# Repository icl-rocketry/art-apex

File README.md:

# art-apex
PCBs and software for ART's APEX rocket

# Contents

1. [Hardware](#Hardware)
2. [Software architecture](#SoftwareArchitecture)
3. [Next Steps](#NextSteps)

## Hardware

The flight computer for Apex consists of the following components:

1. [Tiny2040](https://shop.pimoroni.com/products/tiny-2040) microcontroller - for controlling each of the components
2. [BNO085](https://learn.adafruit.com/adafruit-9-dof-orientation-imu-fusion-breakout-bno085) 9DoF IMU - for recording and fusing flight data
3. [DPS310](https://www.infineon.com/cms/en/product/sensor/pressure-sensors/pressure-sensors-for-iot/dps310/) barometer - for recording altitude information
4. [Sim800L](https://nettigo.eu/products/sim800l-gsm-grps-module) GPRS/GSM module - for communication between the flight computer and ground team
5. [Adafruit mini GPS PA1010D](https://www.adafruit.com/product/4415) GPS module - for recovery
6. 3.7V 200maH LiPo battery - for powering the system
7. A 104 decibel speaker - for recovery

The Tiny2040 is connected to the BNO085, DPS310 and PA1010D via an I2C connection using GPIO pins 26 and 27. The Tiny2040 is connected to the Sim800L module via a UART connection using GPIO pins 4 and 5.

The SIM8000L **must** be isolated when the Tiny2040 is connected to USB, or else it will be fried.

## Software

The filesystem on board the Tiny2040 will look like this:
```
📦src
 ┣ 📂lib
 ┃ ┣ 📂adafruit_bno08x
 ┃ ┃ ┣ 📜debug.py
 ┃ ┃ ┣ 📜i2c.py
 ┃ ┃ ┗ 📜__init__.py
 ┃ ┣ 📂adafruit_bus_device
 ┃ ┃ ┣ 📜i2c_device.mpy
 ┃ ┃ ┣ 📜spi_device.mpy
 ┃ ┃ ┗ 📜__init__.py
 ┃ ┣ 📂adafruit_register
 ┃ ┃ ┣ 📜i2c_bcd_alarm.mpy
 ┃ ┃ ┣ 📜i2c_bcd_datetime.mpy
 ┃ ┃ ┣ 📜i2c_bit.mpy
 ┃ ┃ ┣ 📜i2c_bits.mpy
 ┃ ┃ ┣ 📜i2c_struct.mpy
 ┃ ┃ ┣ 📜i2c_struct_array.mpy
 ┃ ┃ ┗ 📜__init__.py
 ┃ ┣ 📜adafruit_dps310.mpy
 ┃ ┗ 📜adafruit_gps.py
 ┣ 📜boot.py
 ┣ 📜code.py
 ┣ 📜gps.py
 ┣ 📜led.py
 ┣ 📜phone.number
 ┣ 📜sensors.py
 ┣ 📜sms.py
 ┣ 📜speaker.py
 ┗ 📜state_machine.py
```

All folders inside the lib directory are libraries required for the Tiny2040 to interact with components. None of these files should be changed, except for lib/adafruit_bno08x/\_\_init__.py, where `_DEFAULT_REPORT_INTERVAL` should be set to 35ms. **Pro tip: don't lower this if you want to launch**.

`boot.py` runs right after the Tiny2040 boots up. Its sole purpose is to grant write permission to the Tiny2040. Due to the implementation of CircuitPython's filesystem either a laptop or the Tiny2040, can write to the Tiny2040's filesystem, so this ensures that the Tiny2040 has this permission.

`code.py` runs the main code of the AAS. It essentially runs through the state machine defined in `state_machine.py`.

`gps.py`, `led.py`, `sensors.py`, `speaker.py` and `sms.py` are [adapters](https://www.tutorialspoint.com/design_pattern/adapter_pattern.htm) around the peripherals discussed above. The adapter pattern is used to decouple the rest of the code from the specifics of these devices.

`state_machine.py` contains the bulk of the flight logic. It describes a (linear) [finite state machine](https://en.wikipedia.org/wiki/Finite-state_machine) with 5 states.

1. Diagnostic - initialises sensors and sends initial messages
2. Calibration - calibrates the BNO085 as described [here](https://www.ceva-dsp.com/wp-content/uploads/2019/10/BNO080_085-Datasheet.pdf) on page 39
3. Preflight - sleeps until the launch command is sent.
4. Flight - records 5 minutes of flight data, and sends data to the telemetry service.
5. Postflight - sends the rocket's location/plays the siren when asked. Also plays the siren once every 30 seconds.

The Flight stage is the most involved, so a brief explanation of its code can be found below.

```py
def run(self):
    i = 0
    led.colour(255, 0, 0)

    #Problem:
    #Sim module will need long (50ms+) waits to work
    #But we can't afford that in a single threaded environment
    #Solution:
    #Use pkt_wait to provide the sleeps
    pkt_wait = 1
    pkt = bytearray(sensors.data_size * 4)
    self._sms.connect()

    while i < self._flight_time:
        pkt_wait -= 1
        i += 1
        start = millis()
        data = self._sensors.get()
        for reading in data:
            self._sensor_storage.write(struct.pack("f", reading))

        if pkt_wait == 0:
            pkt[0:4] = struct.pack("f", data[0]) #time
            for j in range(4):
                pkt[4*j:4*(j+1)] = struct.pack("f", data[j+4])
            
            pkt[20:24] = struct.pack("f", data[10]) #altitude
            pkt_wait = self._sms.send_pkt(pkt)
        end = millis()
        sleep_ms(max(0, self._delay - (end - start)))

    self._sensor_storage.flush()
    self._sensor_storage.close()
    self._sms.disconnect()
    return postflight(self._sms, self._gps)
```

```py
led.colour(255, 0, 0)
```
First the Tiny2040's led is set to red to indicate flight.

```py
pkt_wait = 1
pkt = bytearray(sensors.data_size * 4)
self._sms.connect()
```
This code relates to the telemetry service. The Sim800L will connect to GPRS here (the internet) and send appropriate data via UDP. To save space, it will group several readings into a single packet.

```py
while i < self._flight_time:
    pkt_wait -= 1
    i += 1
    start = millis()
    data = self._sensors.get()
    for reading in data:
        self._sensor_storage.write(struct.pack("f", reading))

    if pkt_wait == 0:
        pkt[0:4] = struct.pack("f", data[0]) #time
        for j in range(4):
            pkt[4*j:4*(j+1)] = struct.pack("f", data[j+4])
        
        pkt[20:24] = struct.pack("f", data[10]) #altitude
        pkt_wait = self._sms.send_pkt(pkt)
    end = millis()
    sleep_ms(max(0, self._delay - (end - start)))
```

This is the main flight loop. It waits for `self._flight_time` readings to occur (assuming each reading takes at most `self._delay` ms).

```py
start = millis()
data = self._sensors.get()
for reading in data:
    self._sensor_storage.write(struct.pack("f", reading))
```
This code takes sensor readings, and records the time that they were taken, then writes them into a file. The values are stored as 32bit floating point numbers, to save space.
Note: the time recorded is milliseconds from the start.

```py
if pkt_wait == 0:
    pkt[0:4] = struct.pack("f", data[0]) #time
    for j in range(4):
        pkt[4*j:4*(j+1)] = struct.pack("f", data[j+4])
    
    pkt[20:24] = struct.pack("f", data[10]) #altitude
    pkt_wait = self._sms.send_pkt(pkt)
```
This adds the readings into the packet defined earlier, and if the packet is full it sends them.

The `pkt_wait` variable is used to solve a problem, which is that the Sim800l needs to wait around 200ms after it's sent a packet, before being able to send another one. However we can't perform this wait in the main loop, as that would lead to large delays in between recordings, so we define the `pkt_wait` variable to indicate whether we can send a packet. This allows us to use the main loop as a pseudo sleep (at the time of writing, the `uasynchio` library was not available).

```py
end = millis()
sleep_ms(max(0, self._delay - (end - start)))
```
This ensures that we always sleep for at least 50ms, regardless of how long different components take to work.

```py
self._sensor_storage.flush()
self._sensor_storage.close()
self._sms.disconnect()
return postflight(self._sms, self._gps)
```
Finally we flush the recordings, and close the file, then disconnect the Sim800L from GPRS and move on to the postflight stage.

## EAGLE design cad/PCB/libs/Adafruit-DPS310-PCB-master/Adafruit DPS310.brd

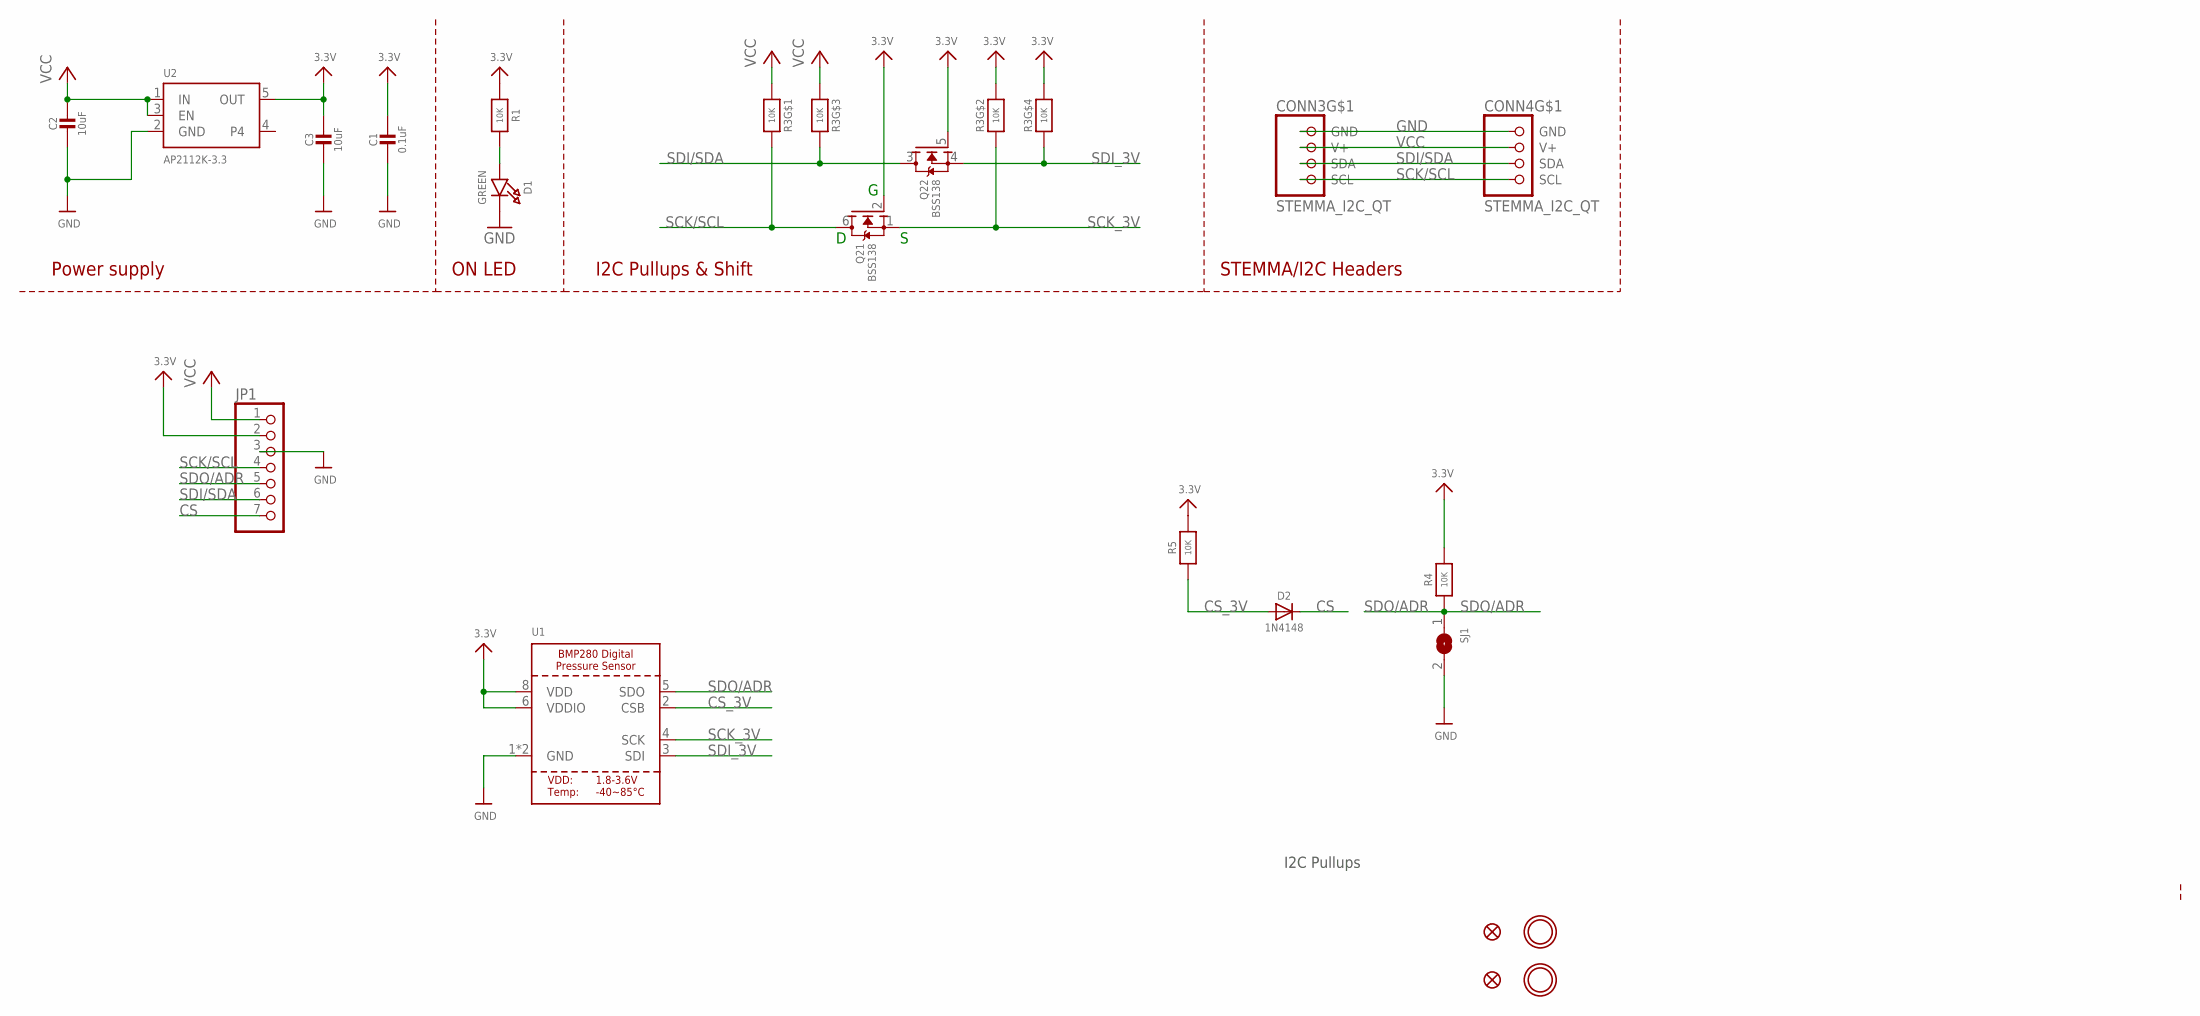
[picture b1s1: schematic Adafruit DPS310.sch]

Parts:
C1: 0.1uF; 0603-NO
C2, C3: 10uF; 0805-NO
CONN3, CONN4: STEMMA_I2C_QT; JST_SH4
D1: GREEN; CHIPLED_0603_NOOUTLINE
D2: 1N4148; SOD-323
FID3, FID4: FIDUCIAL_1MM
JP1: HEADER-1X770MIL; 1X07_ROUND_70
Q2: BSS138; SOT363
R1, R4, R5: 10K; 0603-NO
R3: 10K; RESPACK_4X0603
SJ1: SOLDERJUMPER; SOLDERJUMPER_ARROW_NOPASTE
U1: BMP280_COMBO; BMX280_COMBO
U2: AP2112K-3.3; SOT23-5
U$1, U$17: MOUNTINGHOLE2.5; MOUNTINGHOLE_2.5_PLATED

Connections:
3.3V: C1.1, C3.1, JP1.2, Q2.2 (G), Q2.5 (G), R1.1, R3.2 (1), R3.4 (1), R4.2, R5.2, U1.6 (VDDIO), U1.8 (VDD), U2.5 (OUT)
CS: D2.C, JP1.7
CS_3V: D2.A, R5.1, U1.2 (CSB)
GND: C1.2, C2.2, C3.2, CONN3.1 (GND), CONN4.1 (GND), D1.C, JP1.3, SJ1.2, U1.1 (GND), U1.7 (GND), U2.2 (GND)
unnamed: D1.A, R1.2
SCK/SCL: CONN3.4 (SCL), CONN4.4 (SCL), JP1.4, Q2.6 (D), R3.8 (2)
SCK_3V: Q2.1 (S), R3.7 (2), U1.4 (SCK)
SDI/SDA: CONN3.3 (SDA), CONN4.3 (SDA), JP1.6, Q2.3 (D), R3.6 (2)
SDI_3V: Q2.4 (S), R3.5 (2), U1.3 (SDI)
SDO/ADR: JP1.5, R4.1, SJ1.1, U1.5 (SDO)
VCC: C2.1, CONN3.2 (V+), CONN4.2 (V+), JP1.1, R3.1, R3.3 (1), U2.1 (IN), U2.3 (EN)

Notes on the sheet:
I2C Pullups & Shift
STEMMA/I2C Headers
ON LED
Power supply
I2C Pullups

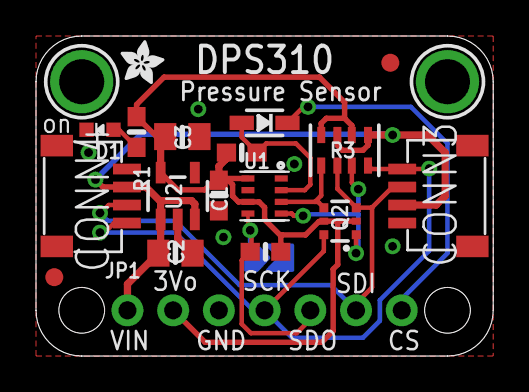
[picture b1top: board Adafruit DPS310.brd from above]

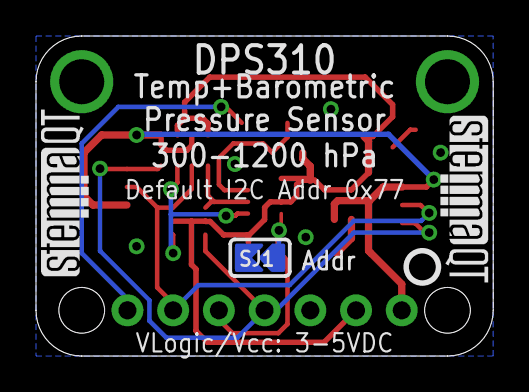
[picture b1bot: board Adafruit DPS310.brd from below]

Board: 2 copper layers, 25.4 x 17.8 mm, 24 parts (4 on the bottom side), 11 nets.

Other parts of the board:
U$4: ADAFRUIT_2.5MM
U$25: PCBFEAT-REV-040
U$30, U$31: STEMMAQT

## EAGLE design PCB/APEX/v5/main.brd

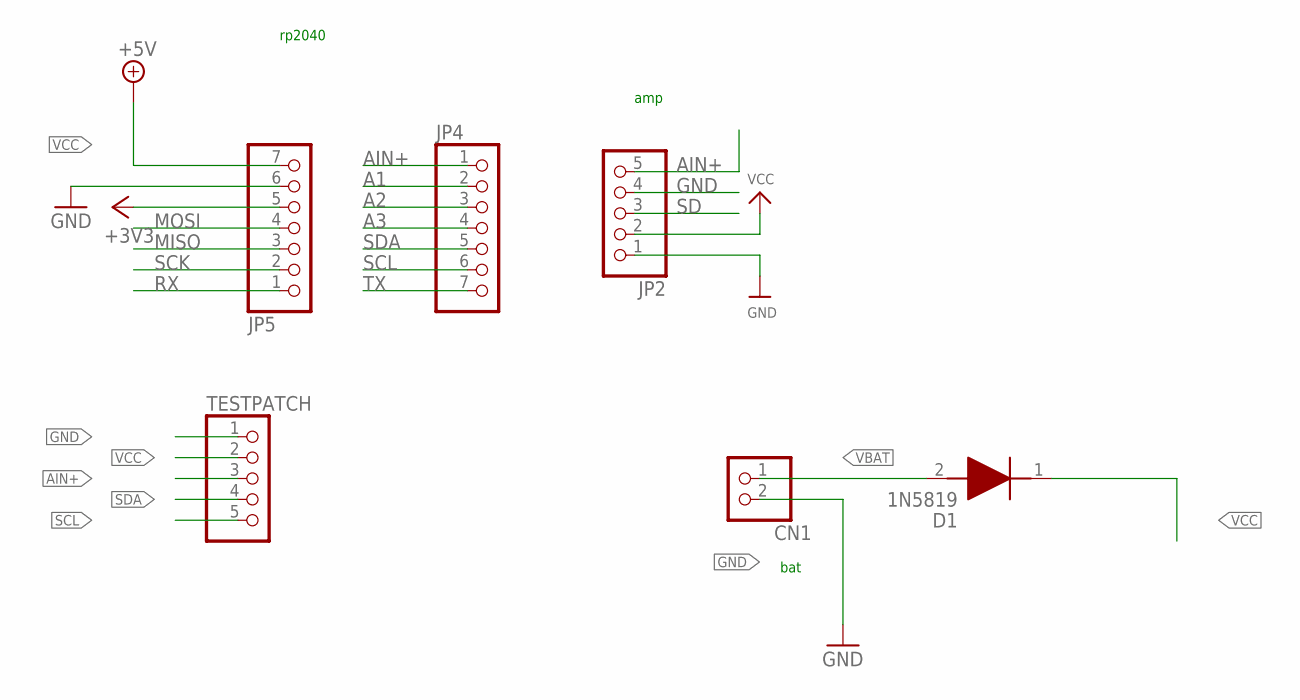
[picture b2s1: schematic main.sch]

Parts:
CN1: JST_2PIN-THM; JST-PH-2-THM
D1: 1N5819; DIOAD1414W86L464D238
JP2: HEADER-1X570MIL; 1X05_ROUND_70
JP4, JP5: HEADER-1X7; 1X07_OVAL
TESTPATCH: PINHD-1X5; 1X05

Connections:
+3V3: JP5.5
A1: JP4.2
A2: JP4.3
A3: JP4.4
AIN+: JP2.5, JP4.1, TESTPATCH.3
GND: CN1.2 (1), JP2.1, JP2.4, JP5.6, TESTPATCH.1
MISO: JP5.3
MOSI: JP5.4
RX: JP5.1
SCK: JP5.2
SCL: JP4.6, TESTPATCH.5
SD: JP2.3
SDA: JP4.5, TESTPATCH.4
TX: JP4.7
VBAT: CN1.1 (2), D1.2 (A)
VCC: D1.1 (K), JP2.2, JP5.7, TESTPATCH.2

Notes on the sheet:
amp
bat
rp2040

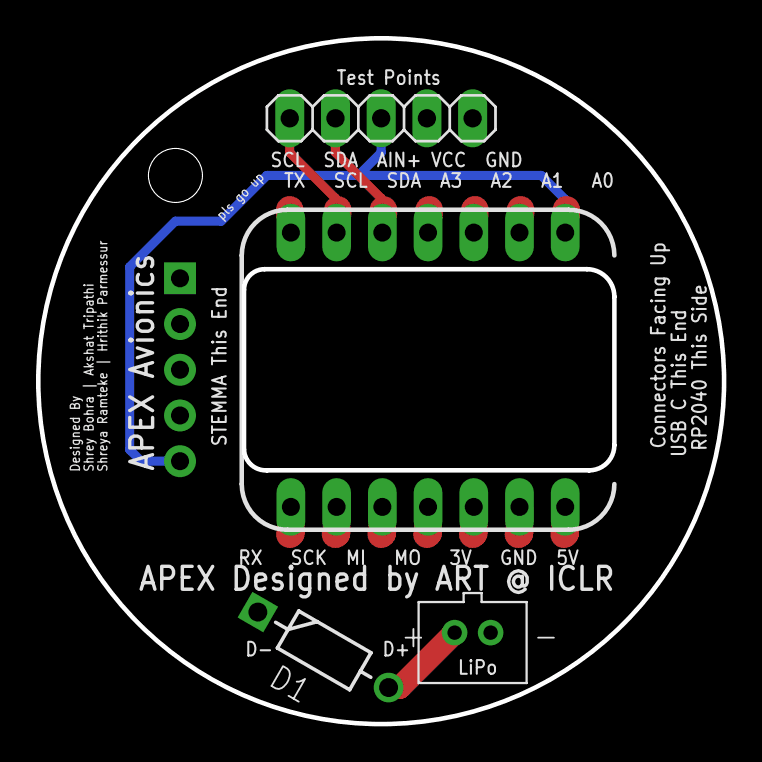
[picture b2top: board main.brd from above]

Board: 2 copper layers, 38.1 x 38.1 mm, 6 parts (1 on the bottom side), 6 nets.

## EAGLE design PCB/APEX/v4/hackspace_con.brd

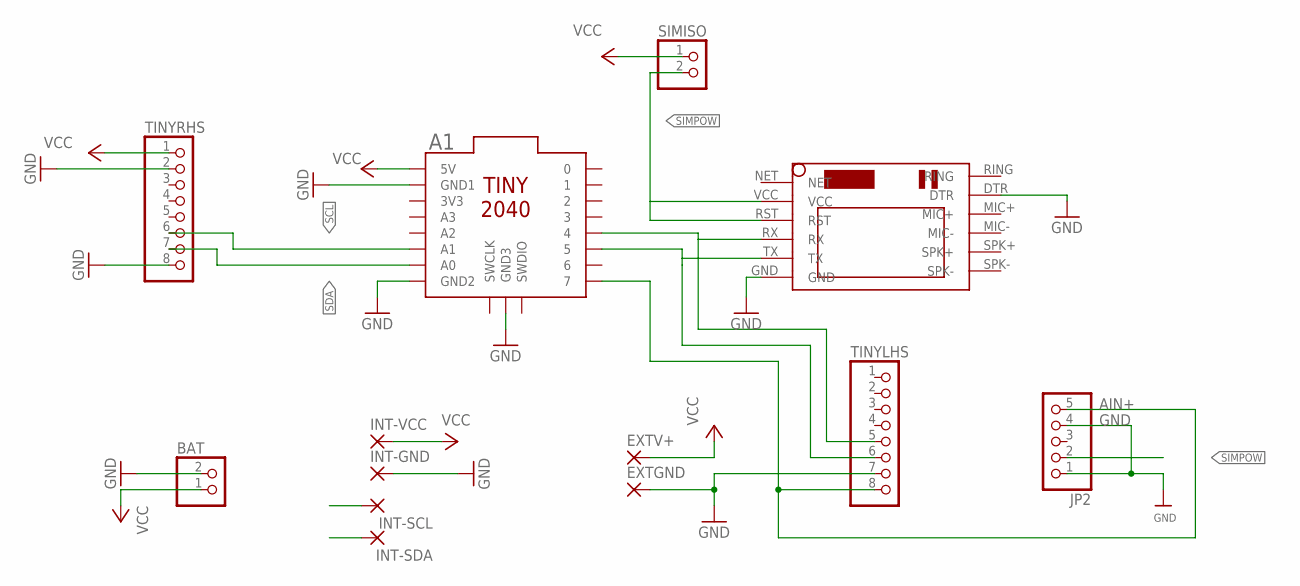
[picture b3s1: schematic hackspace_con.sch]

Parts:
A1: TINY2040
BAT: JST_2PIN-THM-RA; JST-PH-2-THM-RA
EXTGND: SMD5; SMD2,54-5,08
EXTV+: SMD5; SMD2,54-5,08
INT-GND: 3,17/1,1
INT-SCL: 3,17/1,1
INT-SDA: 3,17/1,1
INT-VCC: 3,17/1,1
JP2: HEADER-1X570MIL; 1X05_ROUND_70
SIMISO: PINHD-1X2; 1X02
TINYLHS: PINHD-1X8; 1X08
TINYRHS: PINHD-1X8; 1X08
U$1: SIM800LMODULE

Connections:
AIN+: A1.7, JP2.5, TINYLHS.8
GND: A1.GND1, A1.GND2, A1.GND3, BAT.2 (1), EXTGND.1, INT-GND.1, JP2.1, JP2.4, TINYLHS.7, TINYRHS.2, TINYRHS.8, U$1.DTR, U$1.GND
RX: A1.4, TINYLHS.5, U$1.RX
SCL: A1.A1, INT-SCL.1, TINYRHS.6
SDA: A1.A0, INT-SDA.1, TINYRHS.7
SIMPOW: JP2.2, SIMISO.2, U$1.RST, U$1.VCC
TX: A1.5, TINYLHS.6, U$1.TX
VCC: A1.5V, BAT.1 (2), EXTV+.1, INT-VCC.1, SIMISO.1, TINYRHS.1

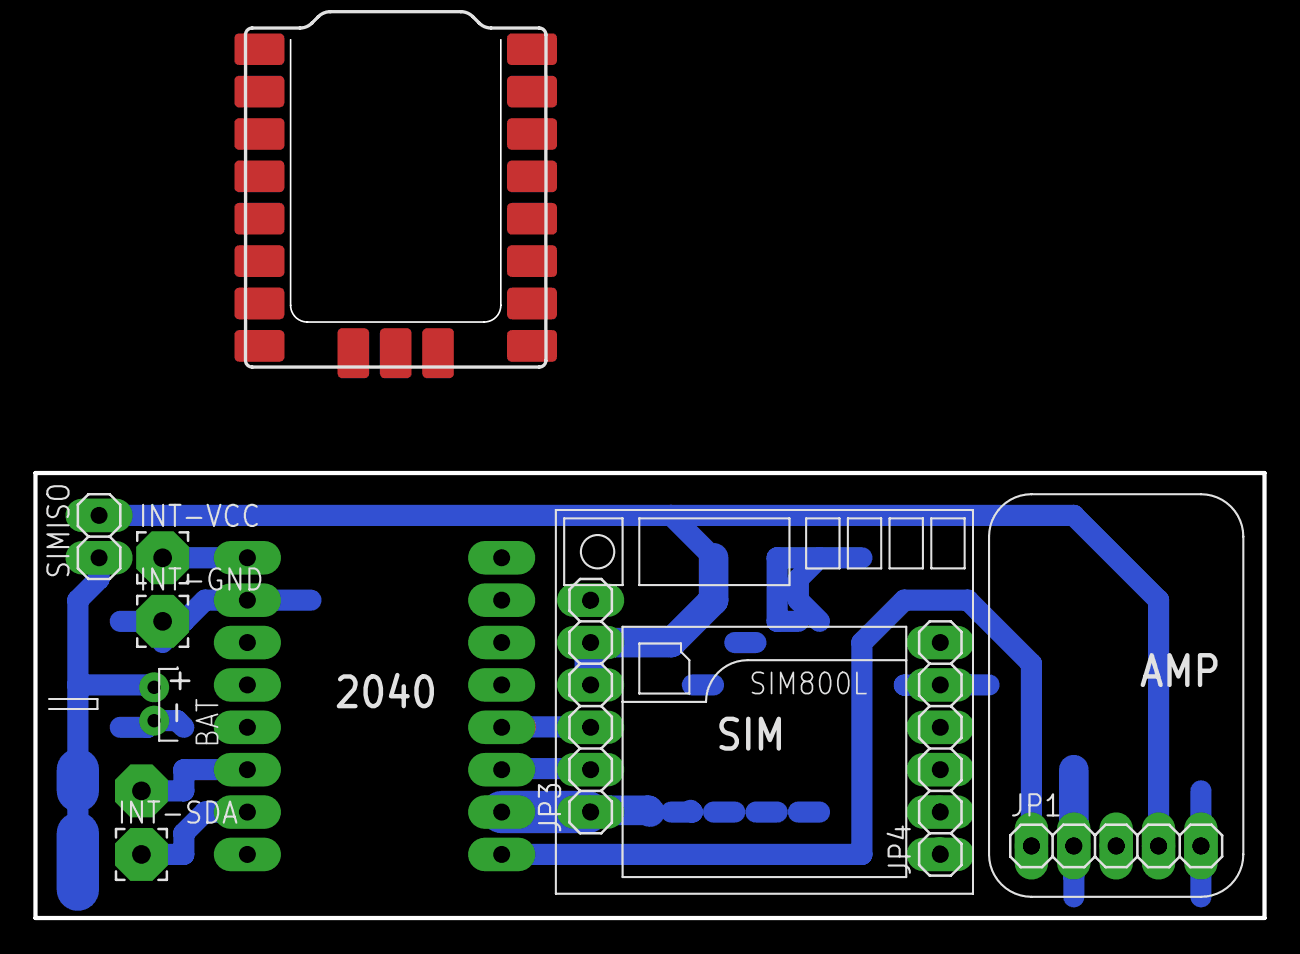
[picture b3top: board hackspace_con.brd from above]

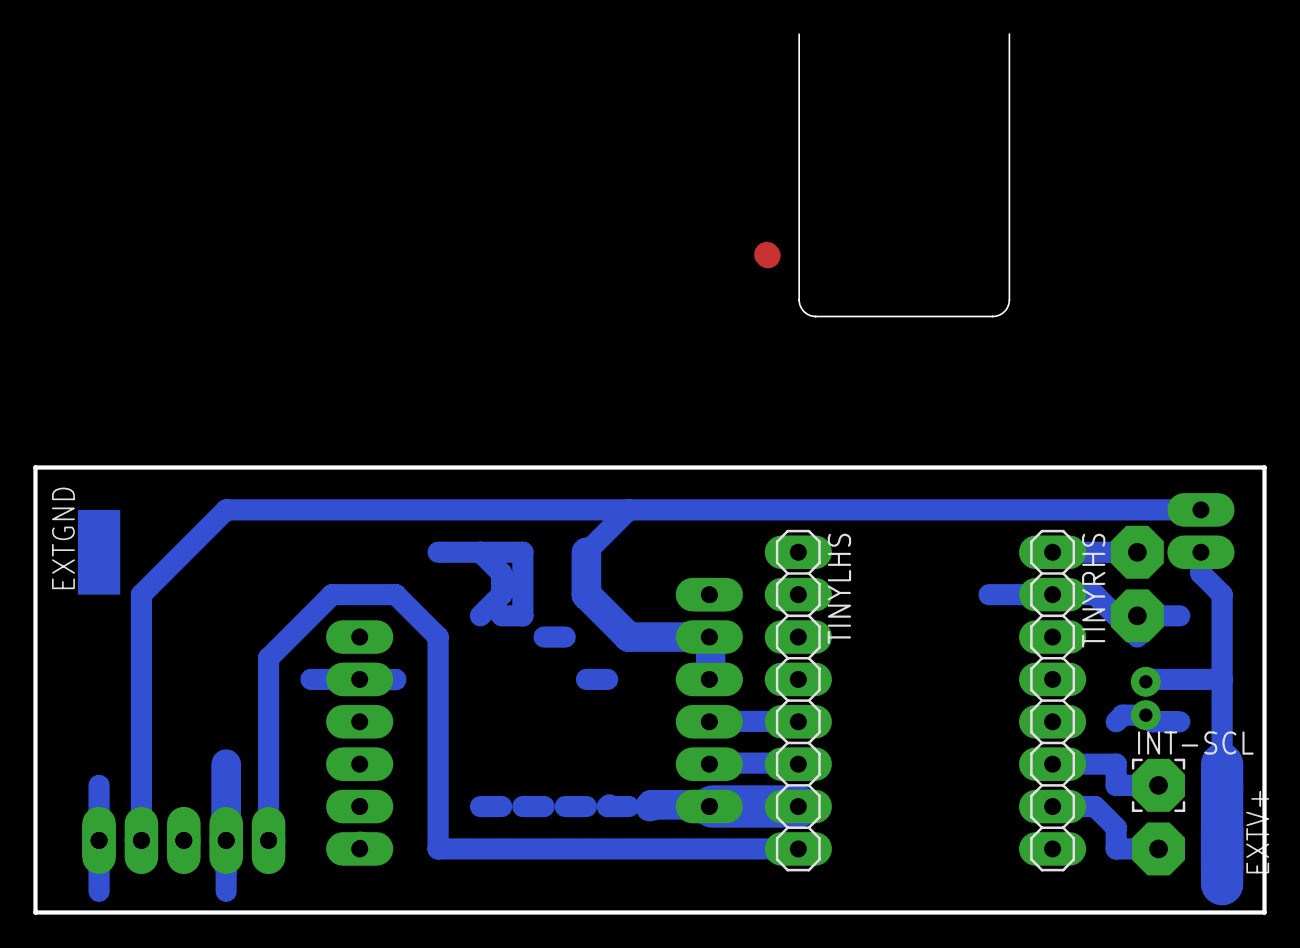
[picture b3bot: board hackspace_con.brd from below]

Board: 2 copper layers, 73.7 x 26.7 mm, 16 parts (5 on the bottom side), 8 nets.

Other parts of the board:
JP1: 1X05
JP3, JP4: 1X06

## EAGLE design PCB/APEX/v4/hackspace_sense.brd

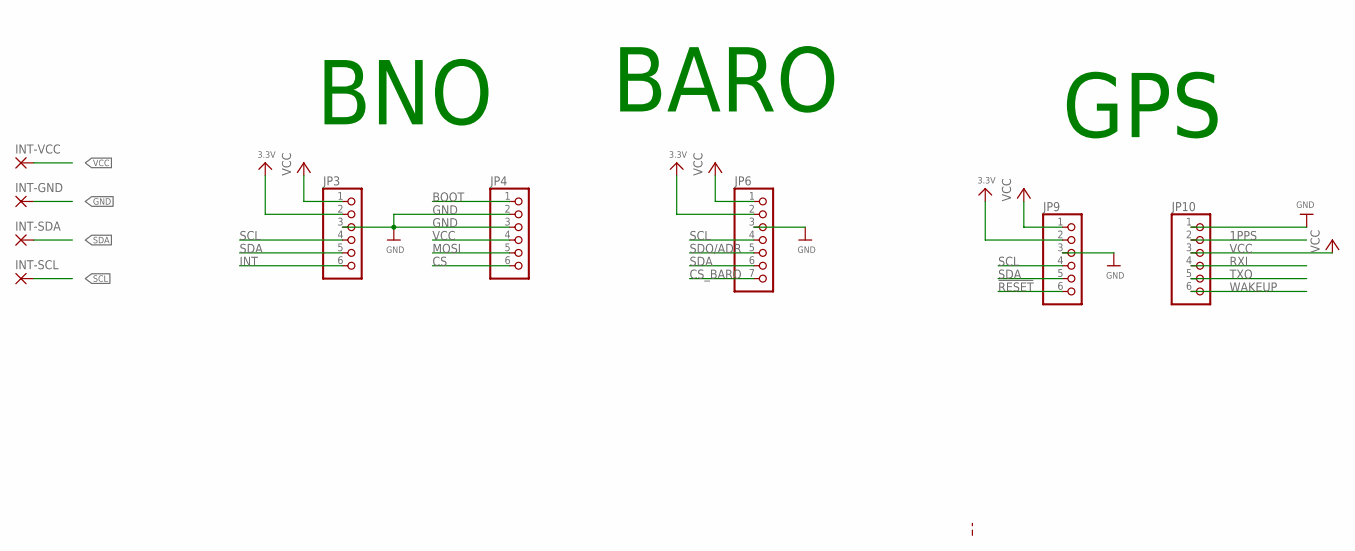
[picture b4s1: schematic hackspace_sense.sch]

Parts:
INT-GND: 3,17/1,1
INT-SCL: 3,17/1,1
INT-SDA: 3,17/1,1
INT-VCC: 3,17/1,1
JP3, JP4, JP9, JP10: HEADER-1X670MIL; 1X06_ROUND_70
JP6: HEADER-1X770MIL; 1X07_ROUND_70

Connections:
1PPS: JP10.2
3.3V_BARO: JP6.2
3.3V_BNO: JP3.2
3.3V_GPS: JP9.2
!RESET: JP9.6
BOOT: JP4.1
CS: JP4.6
CS_BARO: JP6.7
GND: INT-GND.1, JP3.3, JP4.2, JP4.3, JP6.3, JP9.3, JP10.1
INT: JP3.6
MOSI: JP4.5
RXI: JP10.4
SCL: INT-SCL.1, JP3.4, JP6.4, JP9.4
SDA: INT-SDA.1, JP3.5, JP6.6, JP9.5
SDO/ADR: JP6.5
TXO: JP10.5
VCC: INT-VCC.1, JP3.1, JP4.4, JP6.1, JP9.1, JP10.3
WAKEUP: JP10.6

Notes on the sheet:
BNO
BARO
GPS

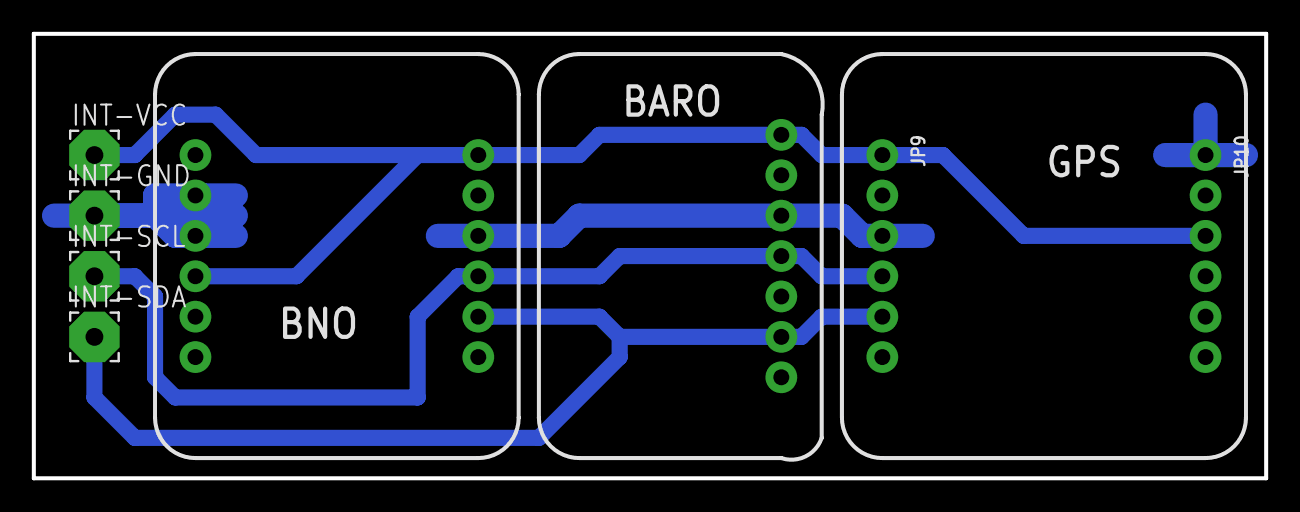
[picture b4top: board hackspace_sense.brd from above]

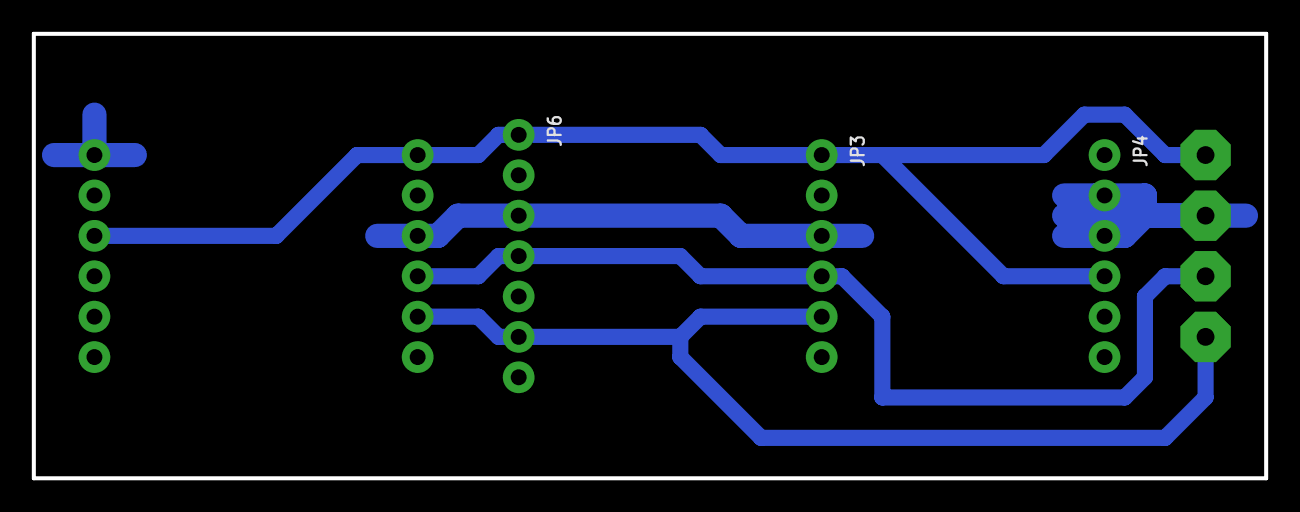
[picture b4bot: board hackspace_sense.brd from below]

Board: 2 copper layers, 77.5 x 27.9 mm, 9 parts (3 on the bottom side), 4 nets.

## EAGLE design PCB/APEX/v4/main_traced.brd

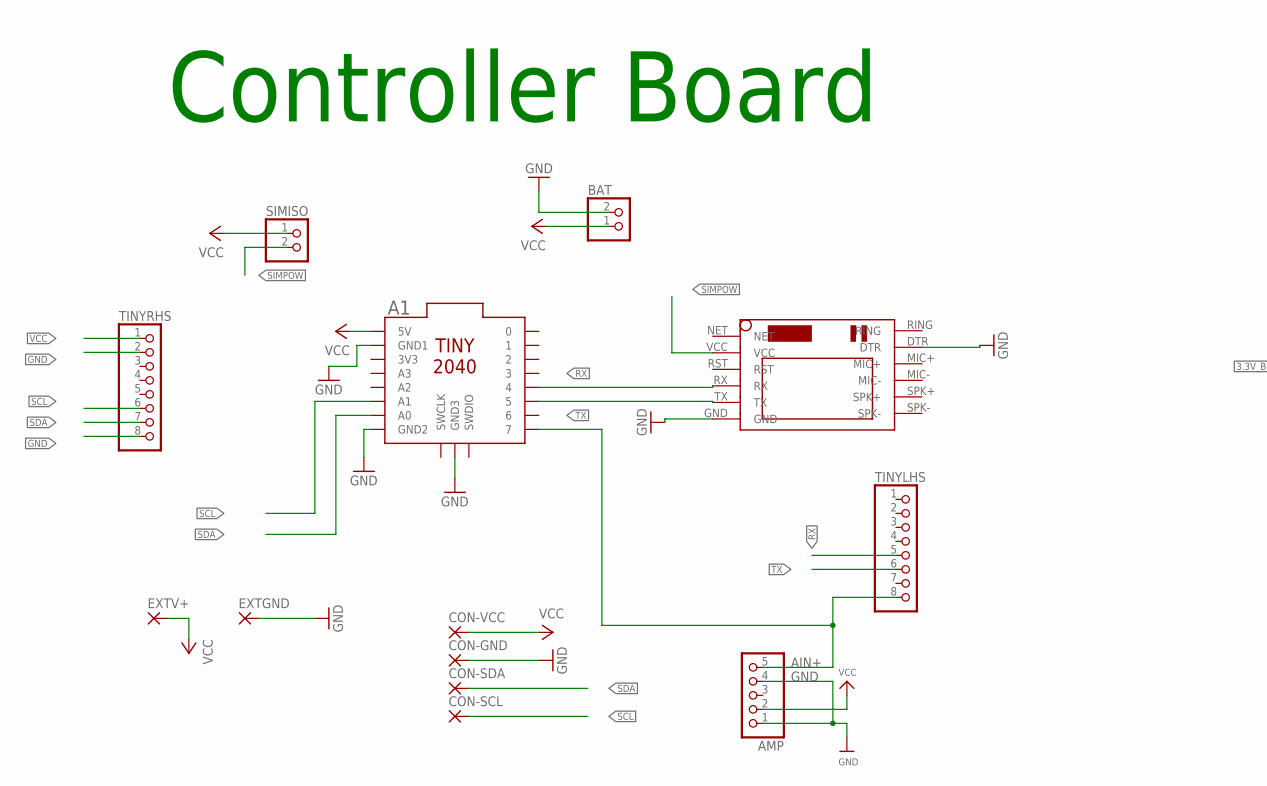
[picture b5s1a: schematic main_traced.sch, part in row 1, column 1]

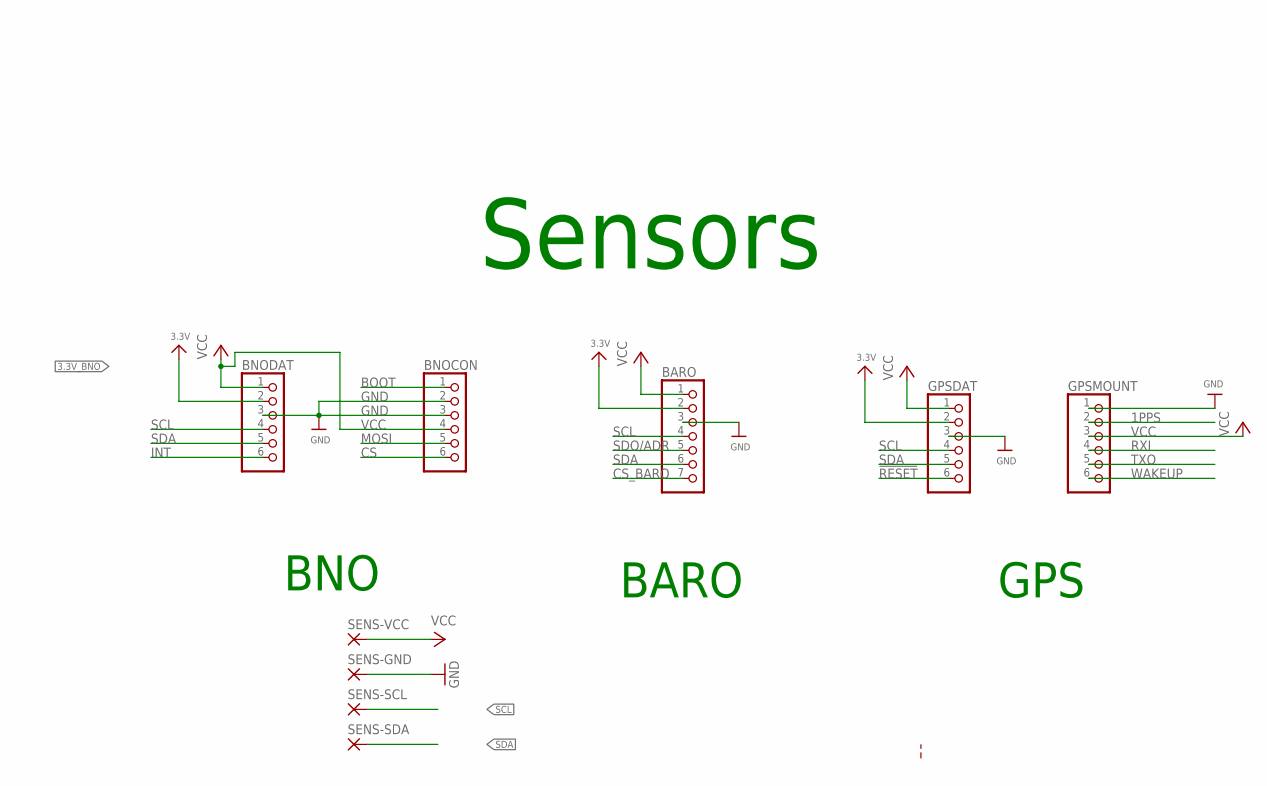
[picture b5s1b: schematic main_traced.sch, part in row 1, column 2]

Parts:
A1: TINY2040
AMP: HEADER-1X570MIL; 1X05_ROUND_70
BARO: HEADER-1X770MIL; 1X07_ROUND_70
BAT: JST_2PIN-THM-RA; JST-PH-2-THM-RA
BNOCON: HEADER-1X670MIL; 1X06_ROUND_70
BNODAT: HEADER-1X670MIL; 1X06_ROUND_70
CON-GND: 3,17/1,3
CON-SCL: 3,17/1,3
CON-SDA: 3,17/1,3
CON-VCC: 3,17/1,3
EXTGND: SMD5; SMD2,54-5,08
EXTV+: SMD5; SMD2,54-5,08
GPSDAT: HEADER-1X670MIL; 1X06_ROUND_70
GPSMOUNT: HEADER-1X670MIL; 1X06_ROUND_70
SENS-GND: 3,17/1,3
SENS-SCL: 3,17/1,3
SENS-SDA: 3,17/1,3
SENS-VCC: 3,17/1,3
SIMISO: PINHD-1X2; 1X02
TINYLHS: PINHD-1X8; 1X08
TINYRHS: PINHD-1X8; 1X08
U$1: SIM800LMODULE

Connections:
1PPS: GPSMOUNT.2
3.3V_2: BARO.2
3.3V_3: GPSDAT.2
3.3V_BNO: BNODAT.2
!RESET: GPSDAT.6
AIN+: A1.7, AMP.5, TINYLHS.8
BOOT: BNOCON.1
CS: BNOCON.6
CS_BARO: BARO.7
GND: A1.GND1, A1.GND2, A1.GND3, AMP.1, AMP.4, BARO.3, BAT.2 (1), BNOCON.2, BNOCON.3, BNODAT.3, CON-GND.1, EXTGND.1, GPSDAT.3, GPSMOUNT.1, SENS-GND.1, TINYRHS.2, TINYRHS.8, U$1.DTR, U$1.GND
INT: BNODAT.6
MOSI: BNOCON.5
RX: A1.4, TINYLHS.5, U$1.RX
RXI: GPSMOUNT.4
SCL: A1.A1, BARO.4, BNODAT.4, CON-SCL.1, GPSDAT.4, SENS-SCL.1, TINYRHS.6
SDA: A1.A0, BARO.6, BNODAT.5, CON-SDA.1, GPSDAT.5, SENS-SDA.1, TINYRHS.7
SDO/ADR: BARO.5
SIMPOW: SIMISO.2, U$1.RST, U$1.VCC
TX: A1.5, TINYLHS.6, U$1.TX
TXO: GPSMOUNT.5
VCC: A1.5V, AMP.2, BARO.1, BAT.1 (2), BNOCON.4, BNODAT.1, CON-VCC.1, EXTV+.1, GPSDAT.1, GPSMOUNT.3, SENS-VCC.1, SIMISO.1, TINYRHS.1
WAKEUP: GPSMOUNT.6

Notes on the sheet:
Controller Board
BNO
BARO
GPS
Sensors

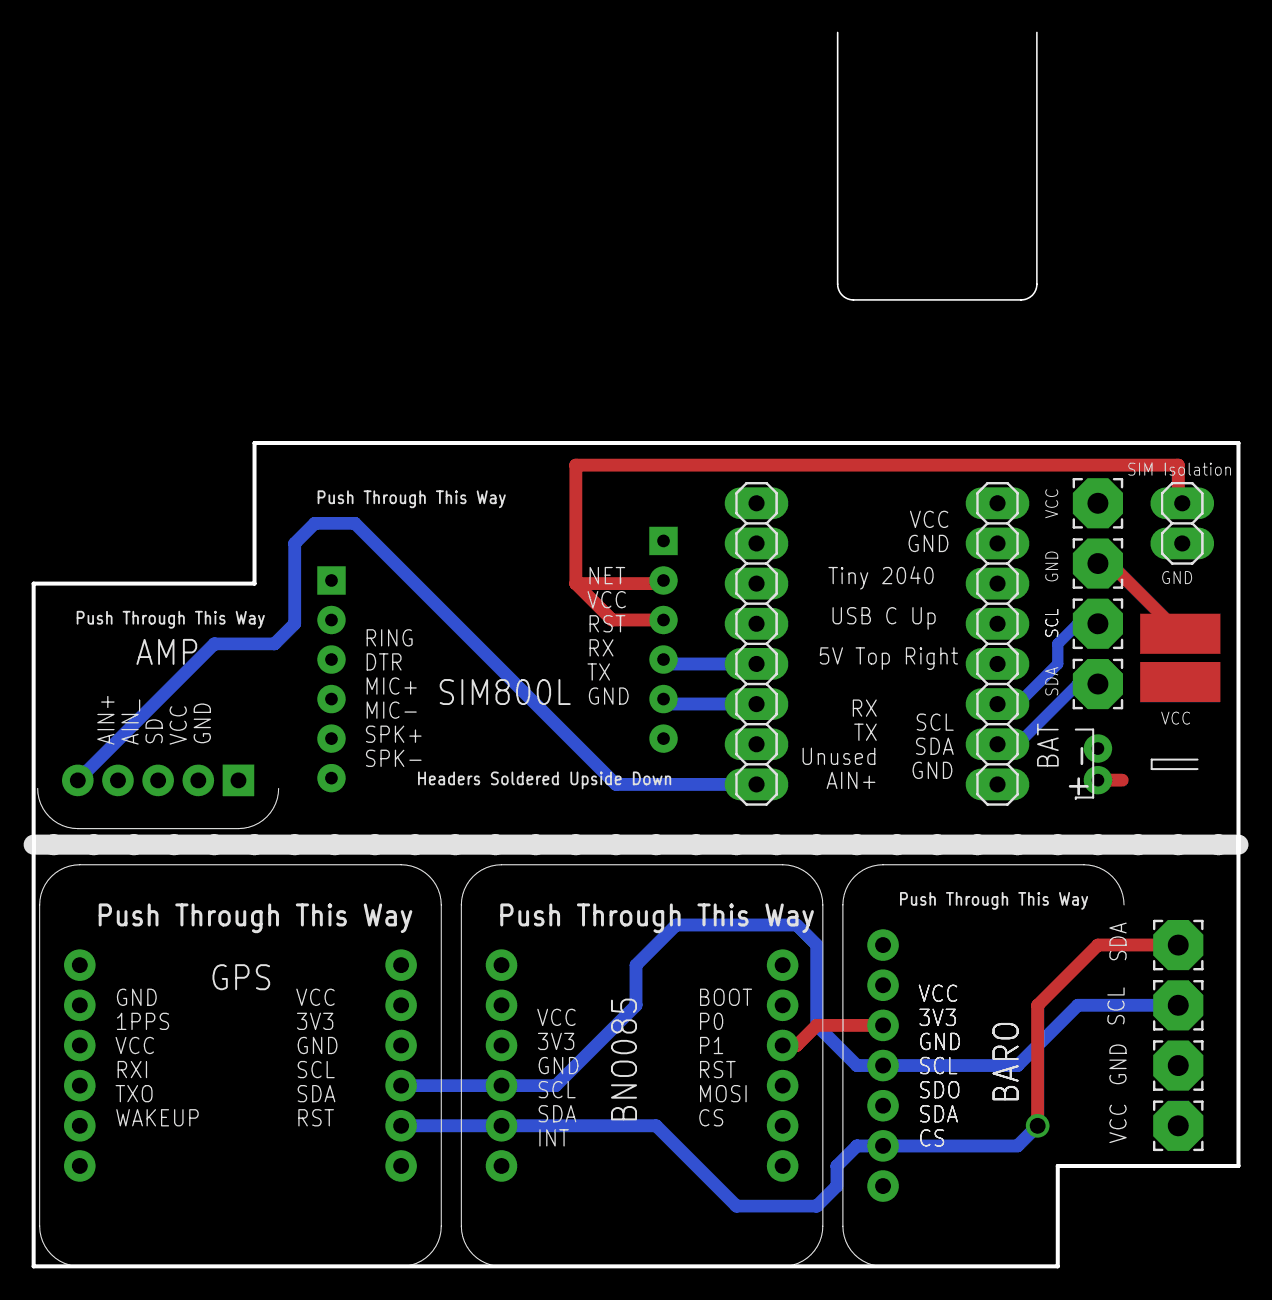
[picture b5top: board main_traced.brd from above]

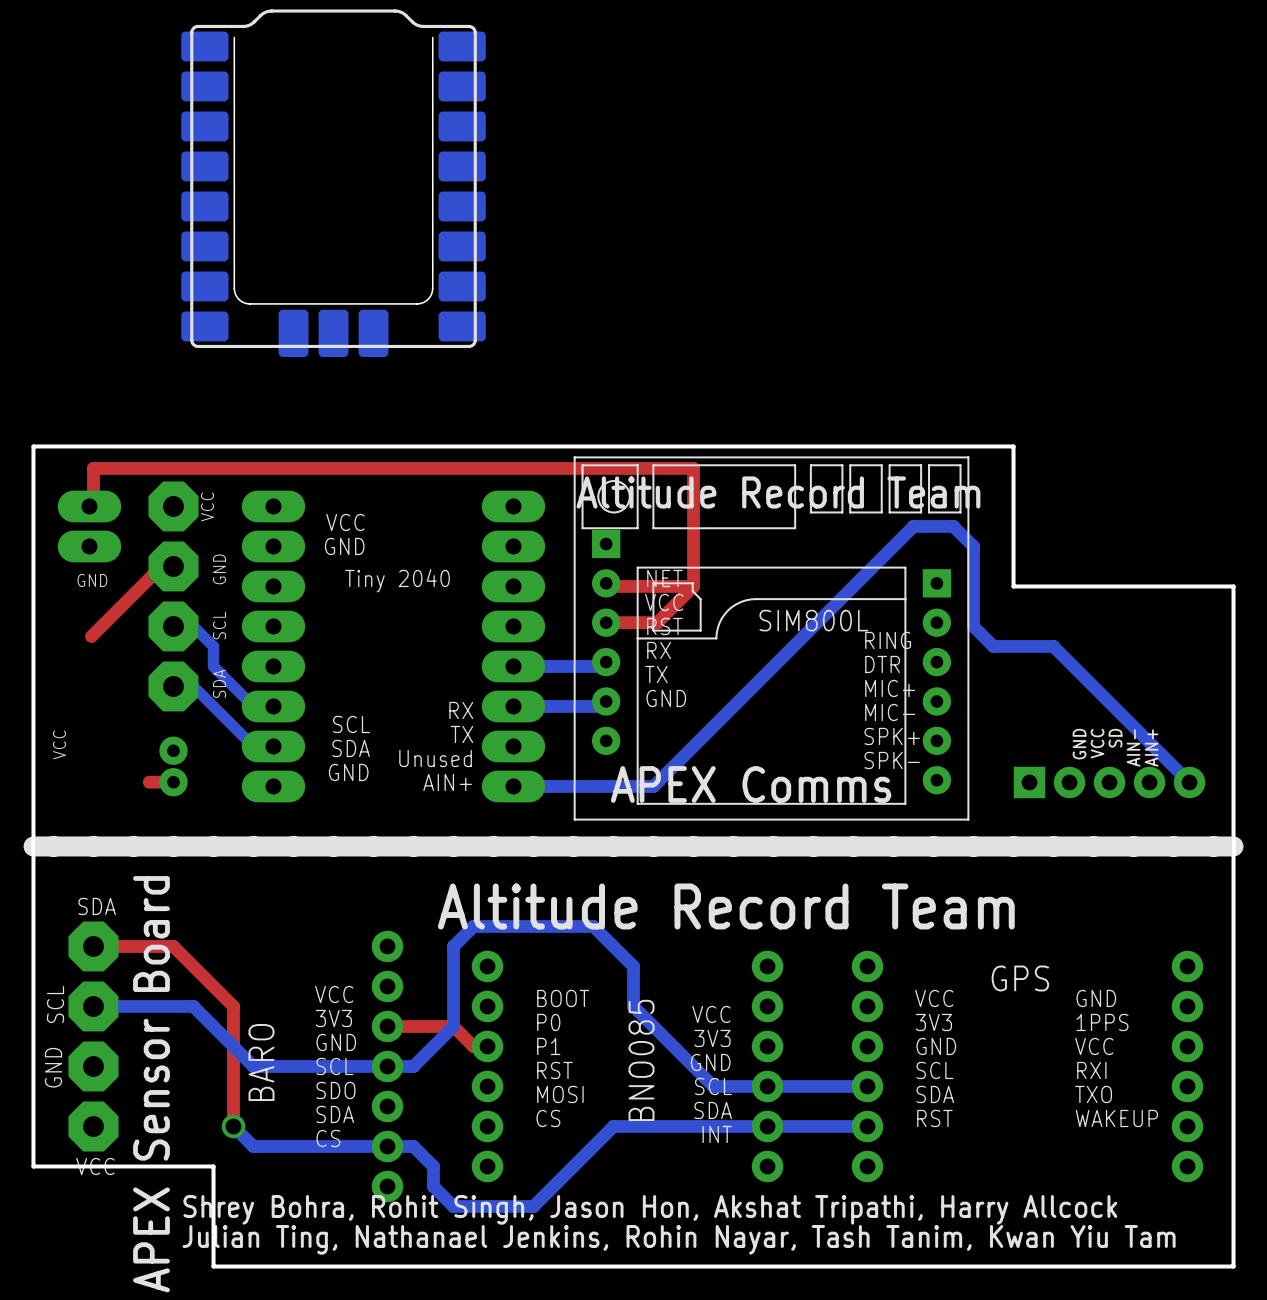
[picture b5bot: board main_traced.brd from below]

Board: 2 copper layers, 76.2 x 52.1 mm, 22 parts (4 on the bottom side), 8 nets.

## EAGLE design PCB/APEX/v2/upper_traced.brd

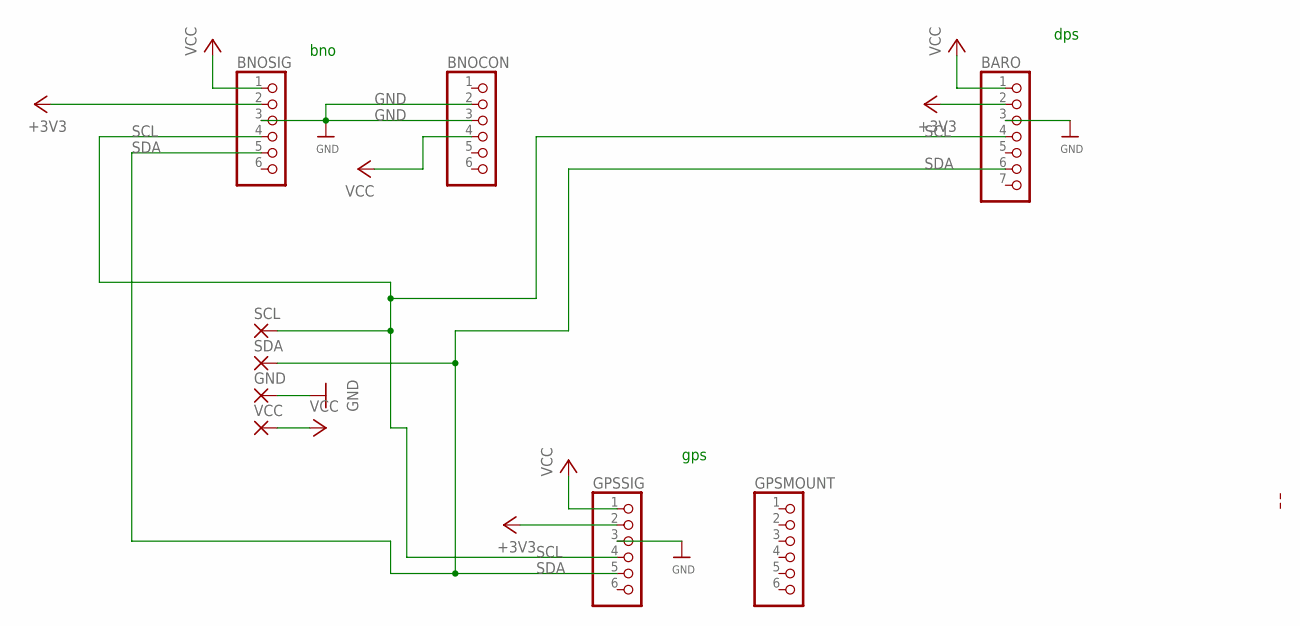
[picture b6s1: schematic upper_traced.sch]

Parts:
BARO: HEADER-1X770MIL; 1X07_ROUND_70
BNOCON: HEADER-1X670MIL; 1X06_ROUND_70
BNOSIG: HEADER-1X670MIL; 1X06_ROUND_70
GND: 3,17/1,1
GPSMOUNT: HEADER-1X670MIL; 1X06_ROUND_70
GPSSIG: HEADER-1X670MIL; 1X06_ROUND_70
SCL: 3,17/1,1
SDA: 3,17/1,1
VCC: 3,17/1,1

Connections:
+3V3: BARO.2, BNOSIG.2, GPSSIG.2
GND: BARO.3, BNOCON.2, BNOCON.3, BNOSIG.3, GND.1, GPSMOUNT.1, GPSSIG.3
SCL: BARO.4, BNOSIG.4, GPSSIG.4, SCL.1
SDA: BARO.6, BNOSIG.5, GPSSIG.5, SDA.1
VCC: BARO.1, BNOCON.4, BNOSIG.1, GPSMOUNT.3, GPSSIG.1, VCC.1

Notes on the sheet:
bno
dps
gps

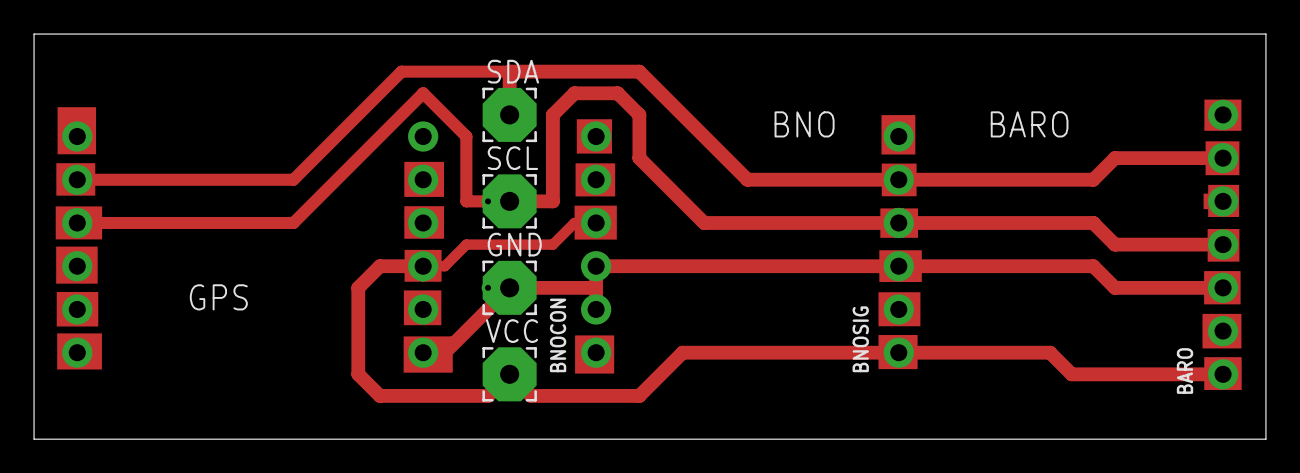
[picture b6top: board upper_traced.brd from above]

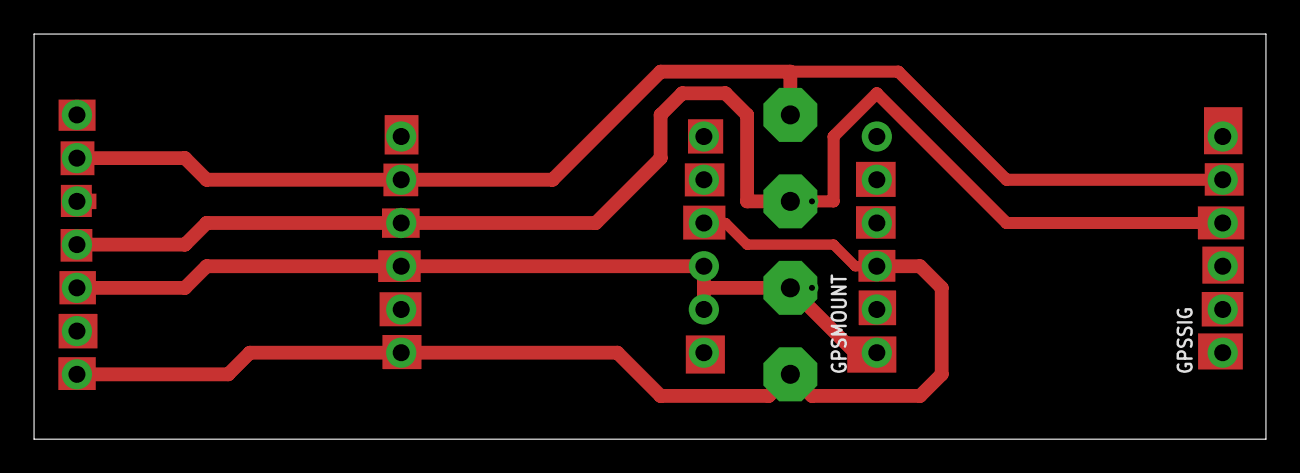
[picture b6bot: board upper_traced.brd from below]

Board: 2 copper layers, 72.4 x 23.8 mm, 9 parts (2 on the bottom side), 5 nets.

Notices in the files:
parts and their libraries:
microbuilder: This work is placed in the public domain, and may be freely used for commercial and non-commercial work with the following conditions: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
